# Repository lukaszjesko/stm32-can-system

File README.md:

# stm32-can-system

I'm a second-year microelectronics student at Poznań University of Technology.
In this project I'm learning the CAN bus and designing my first SMD board.

The goal is a small CAN system with three parts:

1. A USB-CAN adapter: my own board with an STM32G431. A Linux laptop sees it as `can0`.
2. A J1939 node: a board with three power outputs, current measurement and its own buck converter.
3. A Python script on Linux that reads the node's status and switches its outputs through the adapter.

Right now I'm working on the adapter.

## What works

- NUCLEO-G431RB bring-up: LED, `printf` over UART, breakpoints in the debugger
  ([firmware/01-blinky](firmware/01-blinky))
- CAN in loopback mode at 250 kbit/s: the STM32 sends frame `0x123` with 8 data bytes
  and receives it back inside the chip ([firmware/02-can-loopback](firmware/02-can-loopback))
- Two CAN nodes on a real bus at 250 kbit/s: the Nucleo with an SN65HVD230 transceiver
  ([firmware/03-can-two-nodes](firmware/03-can-two-nodes)) and an Arduino Nano with an
  MCP2515 module ([firmware/nano-can](firmware/nano-can)). Each node sends one frame per
  second and the Nucleo prints the frames it gets from the Nano.
- A button on the Nucleo switches an LED on the Nano over CAN, and the Nucleo prints its
  CAN error counters after each frame ([bench test](#bench-test-button--can--led))

Both frames captured on the Nucleo's CAN RX pin (PB8) with a cheap 8-channel logic
analyzer at 4 MHz and decoded in PulseView. One bit takes 4 µs, which is 250 kbit/s.

Frame `0x200` from the Nano:

Frame `0x123` from the Nucleo:

### Bench test: button → CAN → LED

Two nodes on one CAN bus at 250 kbit/s, on a breadboard: a NUCLEO-G431RB with an
SN65HVD230 transceiver and an Arduino Nano with an MCP2515 module. When I press or
release the user button on the Nucleo, it sends frame `0x300` with one data byte
(the button state). The Nano receives it and turns its LED on or off.

After each frame the Nucleo reads the CAN error counters and prints them over UART:

```
state 1
TEC: 0 REC: 0, last error: 0, error passive: 0, bus off: 0
state 0
TEC: 0 REC: 0, last error: 0, error passive: 0, bus off: 0
```

TEC and REC are the transmit and receive error counters. They stay at 0, so every
frame got through without errors.

Code: [firmware/04-can-button](firmware/04-can-button), [firmware/nano-can](firmware/nano-can).

## USB-CAN adapter: PCB ordered

The adapter schematic and 2-layer layout are done in KiCad
([hardware/usb-can-adapter](hardware/usb-can-adapter)). I used the open-source
CANable 2.0 as a reference. The PCB is ordered from JLCPCB and the parts from LCSC.

## What I learned so far

- STM32CubeIDE 2.x no longer includes CubeMX. You set up the chip in CubeMX and import
  the project into the IDE.
- The CAN controller in the STM32G4 has only 3 slots in its transmit queue. Sending in
  a loop without a delay fills it right away.
- On this chip the CAN RX pin (PB8) is also BOOT0. A transceiver keeps RX high, so after
  a reset the chip may start its bootloader instead of my program. The fix is in the
  option bytes (nSWBOOT0 = 0, nBOOT0 = 1). My Nucleo already came set this way, and on
  the adapter I'll set them over SWD.
- A CAN bus needs a 120 Ω resistor at each end. Between CANH and CANL you should measure
  about 60 Ω with the power off. I measured 59 Ω. Before that I got 0 Ω because the
  jumper was on the wrong header and shorted the two lines.
- The PulseView CAN decoder starts at 1 Mbit/s. At the wrong bitrate it shows nonsense
  IDs. Measuring one bit time (4 µs) told me what to set.
- PulseView on my Windows 11 laptop could not open the logic analyzer
  (`LIBUSB_ERROR_NOT_SUPPORTED`, with both WinUSB and libusbK drivers). It works in a
  Linux VM in VirtualBox with USB passthrough.
- I tested CAN errors on purpose. With CAN_H unplugged nobody acknowledges the frame
  (ACK error): TEC goes up by 8 per frame and stops at 128 (error passive). With my own
  TX wire unplugged the node reads back a different bit than it sent (bit error) and
  goes bus-off. It stays off until a reset, so the J1939 node will need bus-off recovery.
- KiCad 10 keeps a local history folder with its own git repository inside. I added it
  to `.gitignore`.

## Next steps

- [x] Two nodes on a real bus, frames decoded in PulseView
- [x] Adapter: finish the schematic and layout, order the PCB
- [ ] Adapter: solder it and get `can0` working on Linux
- [ ] J1939 node: buck converter design, 4-layer PCB, measurements
- [ ] Python script with `python-can` and `cantools`

## Building the firmware

Open a folder from `firmware/` in STM32CubeIDE (File → STM32 Project Create/Import),
build it and run it on a NUCLEO-G431RB. The serial output goes to the ST-LINK COM port
at 115200 8N1.

I write short notes after each session in [docs/lab-notebook.md](docs/lab-notebook.md)
(in Polish).

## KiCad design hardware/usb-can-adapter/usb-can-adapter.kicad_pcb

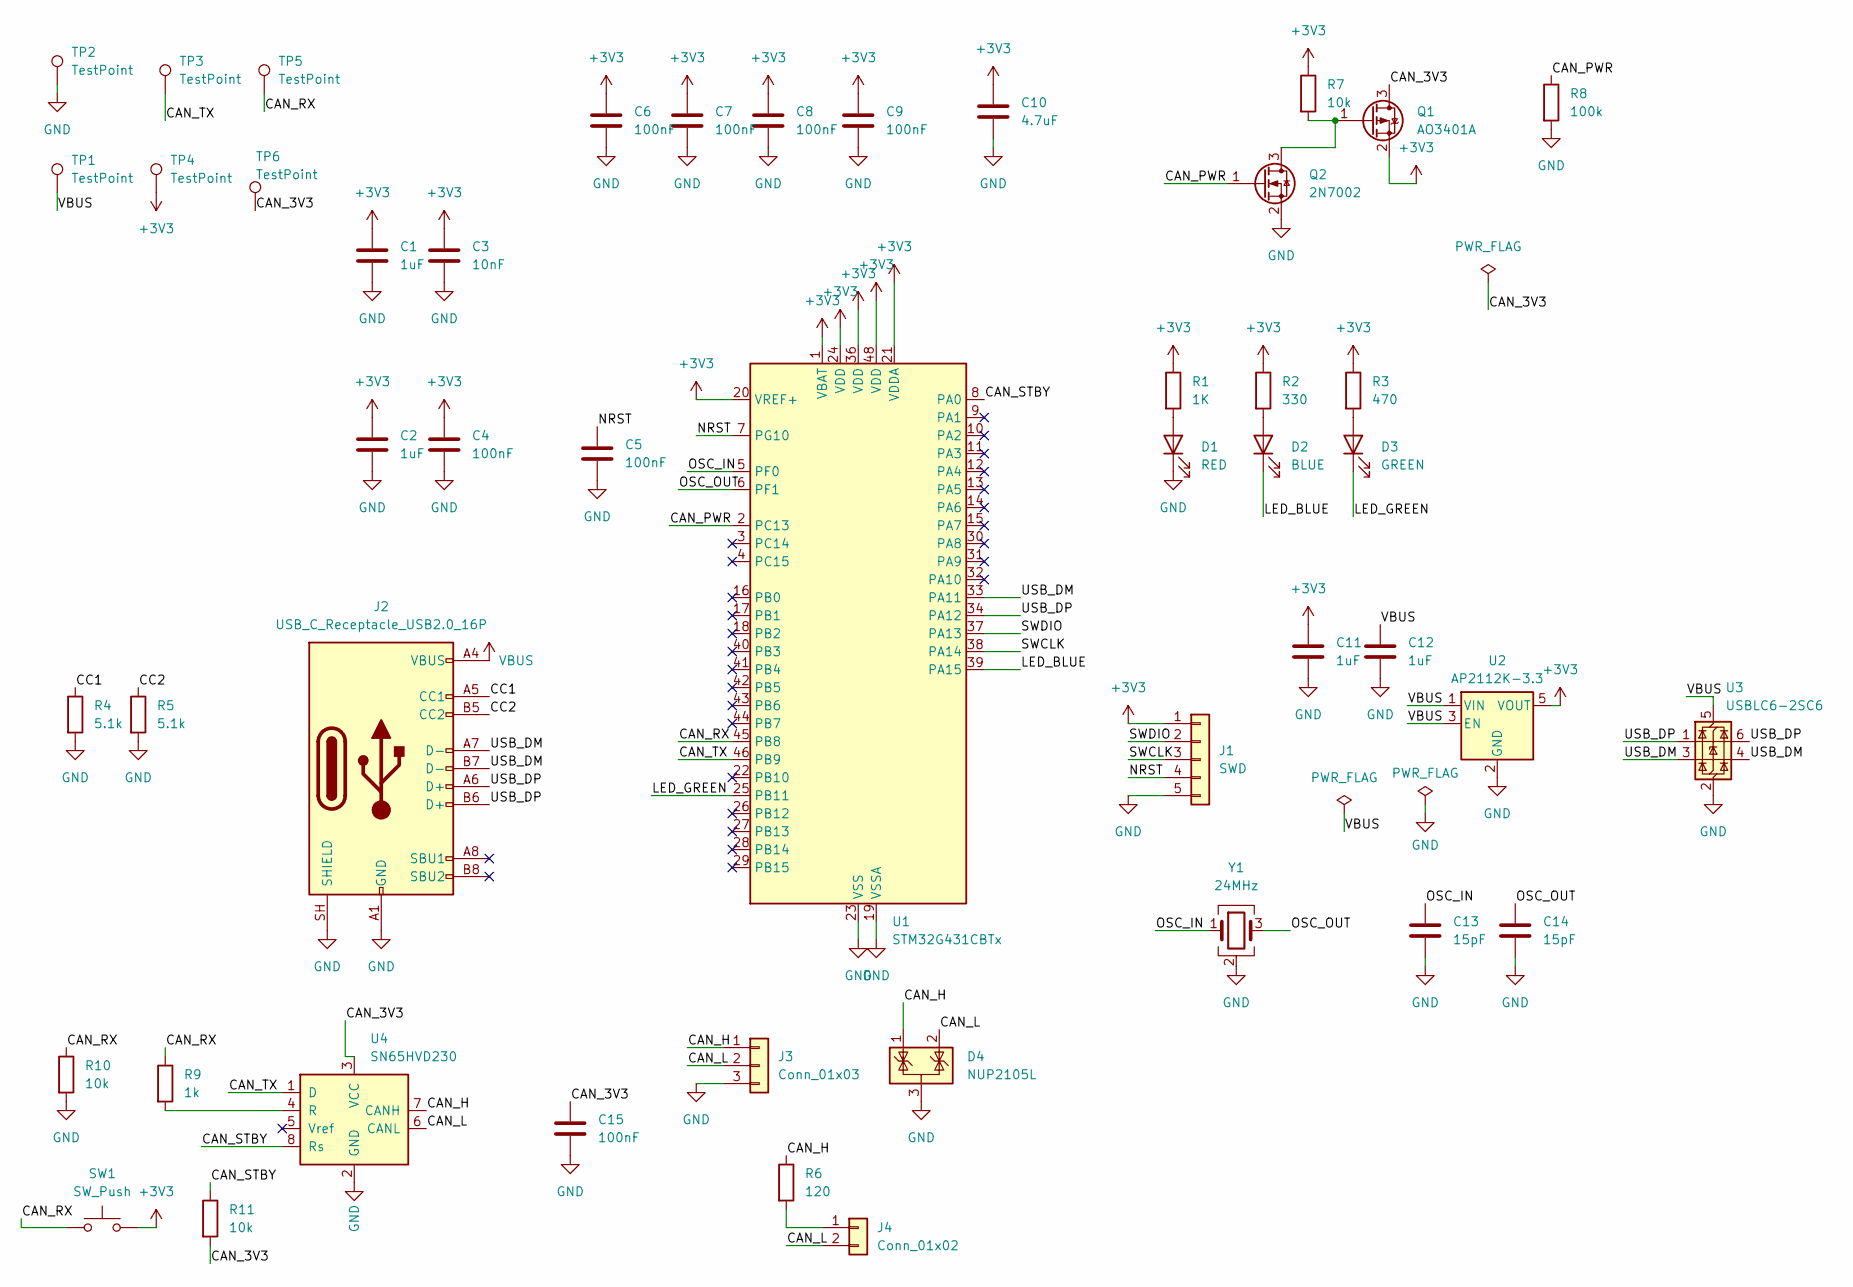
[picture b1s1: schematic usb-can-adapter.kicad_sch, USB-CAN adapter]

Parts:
C1, C2, C11, C12: 1uF; C_0805_2012Metric_Pad1.18x1.45mm_HandSolder
C3: 10nF; C_0805_2012Metric_Pad1.18x1.45mm_HandSolder
C4, C5, C6, C7, C8, C9, C15: 100nF; C_0805_2012Metric_Pad1.18x1.45mm_HandSolder
C10: 4.7uF; C_0805_2012Metric_Pad1.18x1.45mm_HandSolder
C13, C14: 15pF; C_0805_2012Metric_Pad1.18x1.45mm_HandSolder
D1: RED; LED_0805_2012Metric_Pad1.15x1.40mm_HandSolder
D2: BLUE; LED_0805_2012Metric_Pad1.15x1.40mm_HandSolder
D3: GREEN; LED_0805_2012Metric_Pad1.15x1.40mm_HandSolder
D4: NUP2105L; SOT-23
J1: SWD; PinHeader_1x05_P2.54mm_Vertical
J2: USB_C_Receptacle_USB2.0_16P; USB_C_Receptacle_HRO_TYPE-C-31-M-12
J3: Conn_01x03; TerminalBlock_Phoenix_PT-1,5-3-3.5-H_1x03_P3.50mm_Horizontal
J4: Conn_01x02; PinHeader_1x02_P2.54mm_Vertical
Q1: AO3401A; SOT-23
Q2: 2N7002; SOT-23
R1: 1K; R_0805_2012Metric_Pad1.20x1.40mm_HandSolder
R2: 330; R_0805_2012Metric_Pad1.20x1.40mm_HandSolder
R3: 470; R_0805_2012Metric_Pad1.20x1.40mm_HandSolder
R4, R5: 5.1k; R_0805_2012Metric_Pad1.20x1.40mm_HandSolder
R6: 120; R_0805_2012Metric_Pad1.20x1.40mm_HandSolder
R7, R10, R11: 10k; R_0805_2012Metric_Pad1.20x1.40mm_HandSolder
R8: 100k; R_0805_2012Metric_Pad1.20x1.40mm_HandSolder
R9: 1k; R_0805_2012Metric_Pad1.20x1.40mm_HandSolder
SW1: SW_Push; SW_Push_1P1T_XKB_TS-1187A
TP1, TP2, TP3, TP4, TP5, TP6: TestPoint; TestPoint_Pad_D1.5mm
U1: STM32G431CBTx; LQFP-48_7x7mm_P0.5mm
U2: AP2112K-3.3; SOT-23-5
U3: USBLC6-2SC6; SOT-23-6
U4: SN65HVD230; SOIC-8_3.9x4.9mm_P1.27mm
Y1: 24MHz; Crystal_SMD_3225-4Pin_3.2x2.5mm

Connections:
+3V3: C1.1, C2.1, C3.1, C4.1, C6.1, C7.1, C8.1, C9.1, C10.1, C11.1, J1.1, Q1.2 (S), R1.1, R2.1, R3.1, R7.1, SW1.2, TP4.1 (1_1), U1.1 (VBAT), U1.20 (VREF+), U1.21 (VDDA), U1.24 (VDD), U1.36 (VDD), U1.48 (VDD), U2.5 (VOUT)
/CAN_3V3: C15.1, Q1.3 (D), R11.2, TP6.1 (1_1), U4.3 (VCC)
/CAN_H: D4.1 (K), J3.1, R6.1, U4.7 (CANH)
/CAN_L: D4.2 (K), J3.2, J4.2, U4.6 (CANL)
/CAN_PWR: Q2.1 (G), R8.1, U1.2 (PC13)
/CAN_RX: R9.1, R10.1, SW1.1, TP5.1 (1_1), U1.45 (PB8)
/CAN_STBY: R11.1, U1.8 (PA0), U4.8 (Rs)
/CAN_TX: TP3.1 (1_1), U1.46 (PB9), U4.1 (D)
/CC1: J2.A5 (CC1), R4.1
/CC2: J2.B5 (CC2), R5.1
/LED_BLUE: D2.1 (K), U1.39 (PA15)
/LED_GREEN: D3.1 (K), U1.25 (PB11)
/NRST: C5.1, J1.4, U1.7 (PG10)
/OSC_IN: C13.1, U1.5 (PF0), Y1.1
/OSC_OUT: C14.1, U1.6 (PF1), Y1.3
/SWCLK: J1.3, U1.38 (PA14)
/SWDIO: J1.2, U1.37 (PA13)
/USB_DM: J2.A7 (D-), J2.B7 (D-), U1.33 (PA11), U3.3 (I/O2), U3.4 (I/O2)
/USB_DP: J2.A6 (D+), J2.B6 (D+), U1.34 (PA12), U3.1 (I/O1), U3.6 (I/O1)
GND: C1.2, C2.2, C3.2, C4.2, C5.2, C6.2, C7.2, C8.2, C9.2, C10.2, C11.2, C12.2, C13.2, C14.2, C15.2, D1.1 (K), D4.3 (A), J1.5, J2.A1 (GND), J2.A12 (GND), J2.B1 (GND), J2.B12 (GND), J2.SH (SHIELD), J3.3, Q2.2 (S), R4.2, R5.2, R8.2, R10.2, TP2.1 (1_1), U1.19 (VSSA), U1.23 (VSS), U1.35 (VSS), U1.47 (VSS), U2.2 (GND), U3.2 (GND), U4.2 (GND), Y1.2 (G), Y1.4 (G)
unnamed: D1.2 (A), R1.2
unnamed: D2.2 (A), R2.2
unnamed: D3.2 (A), R3.2
unnamed: J4.1, R6.2
unnamed: Q1.1 (G), Q2.3 (D), R7.2
unnamed: R9.2, U4.4 (R)
VBUS: C12.1, J2.A4 (VBUS), J2.A9 (VBUS), J2.B4 (VBUS), J2.B9 (VBUS), TP1.1 (1_1), U2.1 (VIN), U2.3 (EN), U3.5 (VBUS)

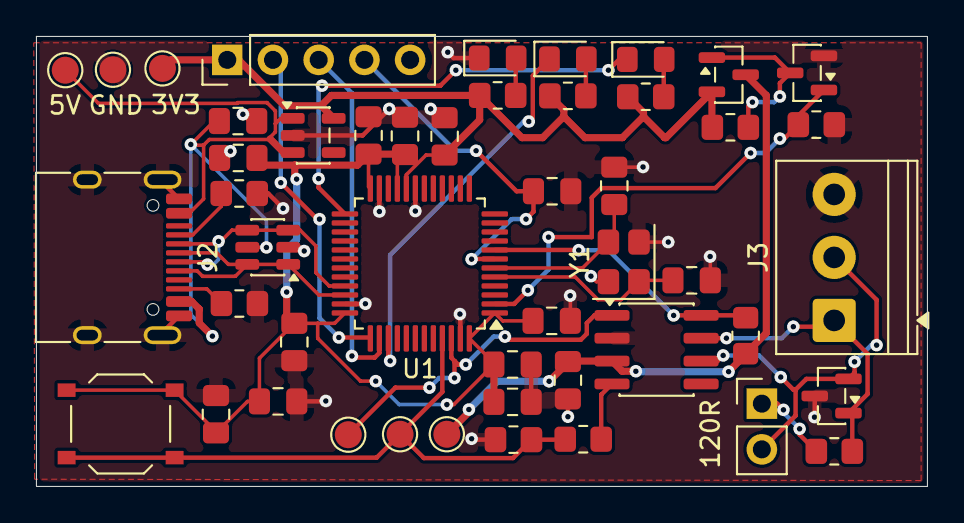
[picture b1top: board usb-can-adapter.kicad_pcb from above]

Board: 2 copper layers, 49.5 x 25.0 mm, 48 parts (0 on the bottom side), 27 nets.
